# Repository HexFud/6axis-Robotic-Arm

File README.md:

## 6 Axis Robotic Arm

I created this 6 axis robotic arm entirely from scratch starting from the PCB to the 3D modelling and designing.

## How this was made

I designed the PCB that can take up to 6 motors (I used 6 NEMA 17) with 6 driver boards that you can directly plug into the PCB. In the PCB case there is a cutout for a 40mm fan directly pluggable into the dedicated +5V socket (identified by FAN or J8 connector), this is foundamental to keep the motor drivers cool and keep things as safe as possible. The board runs on 24V connection and includes connections for:

1. **6 limit switches** for homing each joint
2. **A CAN Bus interface**
3. **An emergency stop button socket** for safety reason. 

## External connections breakdown

1. **E-STOP (J21)** The emergency stop circuit is NC so the board without this button won't power on, if you want to avoid this you can short 2 pins of the J21 connector with a jumper (please mind your safety)
2. **CAN Bus (J22)** This is the port to make the PCB comunicate with the PC and it only has 2 pins CAN_H and CAN_L if you want to send commands directly to the board you need to have a USB-CAN adapter
3. **Power button (J19)** The socket on the PCB has 4 pins
 
| Pin | Function | Where to connect |
| :---: | :--- | :--- |
| **1** | `GND` | Switch contact + LED Negative (`-`) wire |
| **2** | `PWR` | Switch contact |
| **3** | `+3V3` | LED Positive (`+`) wire |
| **4** | `Reserved` | *Do not connect any wire to it* |

## Mechanical design and why I chose certain components

To make sure the arm can lift certain payloads wihout struggling I preferred to not use a direct-drive style to move the joints, this is why for the most heavy and tourqe demanding parts I paired the NEMA 17 motors with 20:1 and 10:1 gearboxes (you can see them marked in red)

## How to flash the firmware

My project doesn't have a USB-C or other type of interfaces so to flash the firmware you need a ST-LINK V2 where you need to wire up the correct cable from the usb to the board (J18 connector) and download the free software [STM32CubeProgrammer](https://www.st.com/content/st_com/en/stm32cubeprogrammer.html) and you simply need to upload the firmware.

Steps to reproduce (note that you need to do both):

In Arduino IDE:
1. Install Arduino IDE
2. Paste https://github.com/stm32duino/BoardManagerFiles/raw/main/package_stmicroelectronics_index.json into prefernces -> additional board manager URL's
3. Search STM32 into the boards stab and install it
4. Go in tools -> board -> STM32 MCU based boards and select Generic STM32F4 series
5. Go in tools -> board part number and select Generic F446RETx
6. Go to sketch -> export compiled binary

In STM32CubeProgrammer:
1. Install the software from the link above
2. Insert the ST-Link V2 USB into the pc
3. Connect the pins explained above (do not connect the 24V power supply, the ST-Link has enough power to power the chip to flash)
4. In STM32CubeProgrammer ensure that ST-LINK is selected and click connect
5. Go in the erasing & programming tab and select the previously exported .bin file
6. Click start programming and if everything went right you'll see Download verified successfully

## Filament reccomendation

Because stepper motors and the drivers generate heat around 50°C-60°C I strongly reccomend to use filaments like PETG, ABS or ASA instead of standard PLA ensuring the plastic won't soften, warp or melt during intensive load.

## ⚠️⚠️ Safety advice ⚠️⚠️

This project includes experimental software, hardware designs, and assembly documentation are still under development and may contain bugs, errors, or incomplete features. By using, building, or modifying this project, you acknowledge that:

1. You use this project entirely at your own risk
2. You are solely responsible for safe assembly, testing, and operation
3. The autor isn't responsible for any type of damage, injury or loss to people or the machine itself

By proceeding, you accept all risks and agree to these conditions. If you do not acknowledge these risks and conditions, please do not use or build this project.

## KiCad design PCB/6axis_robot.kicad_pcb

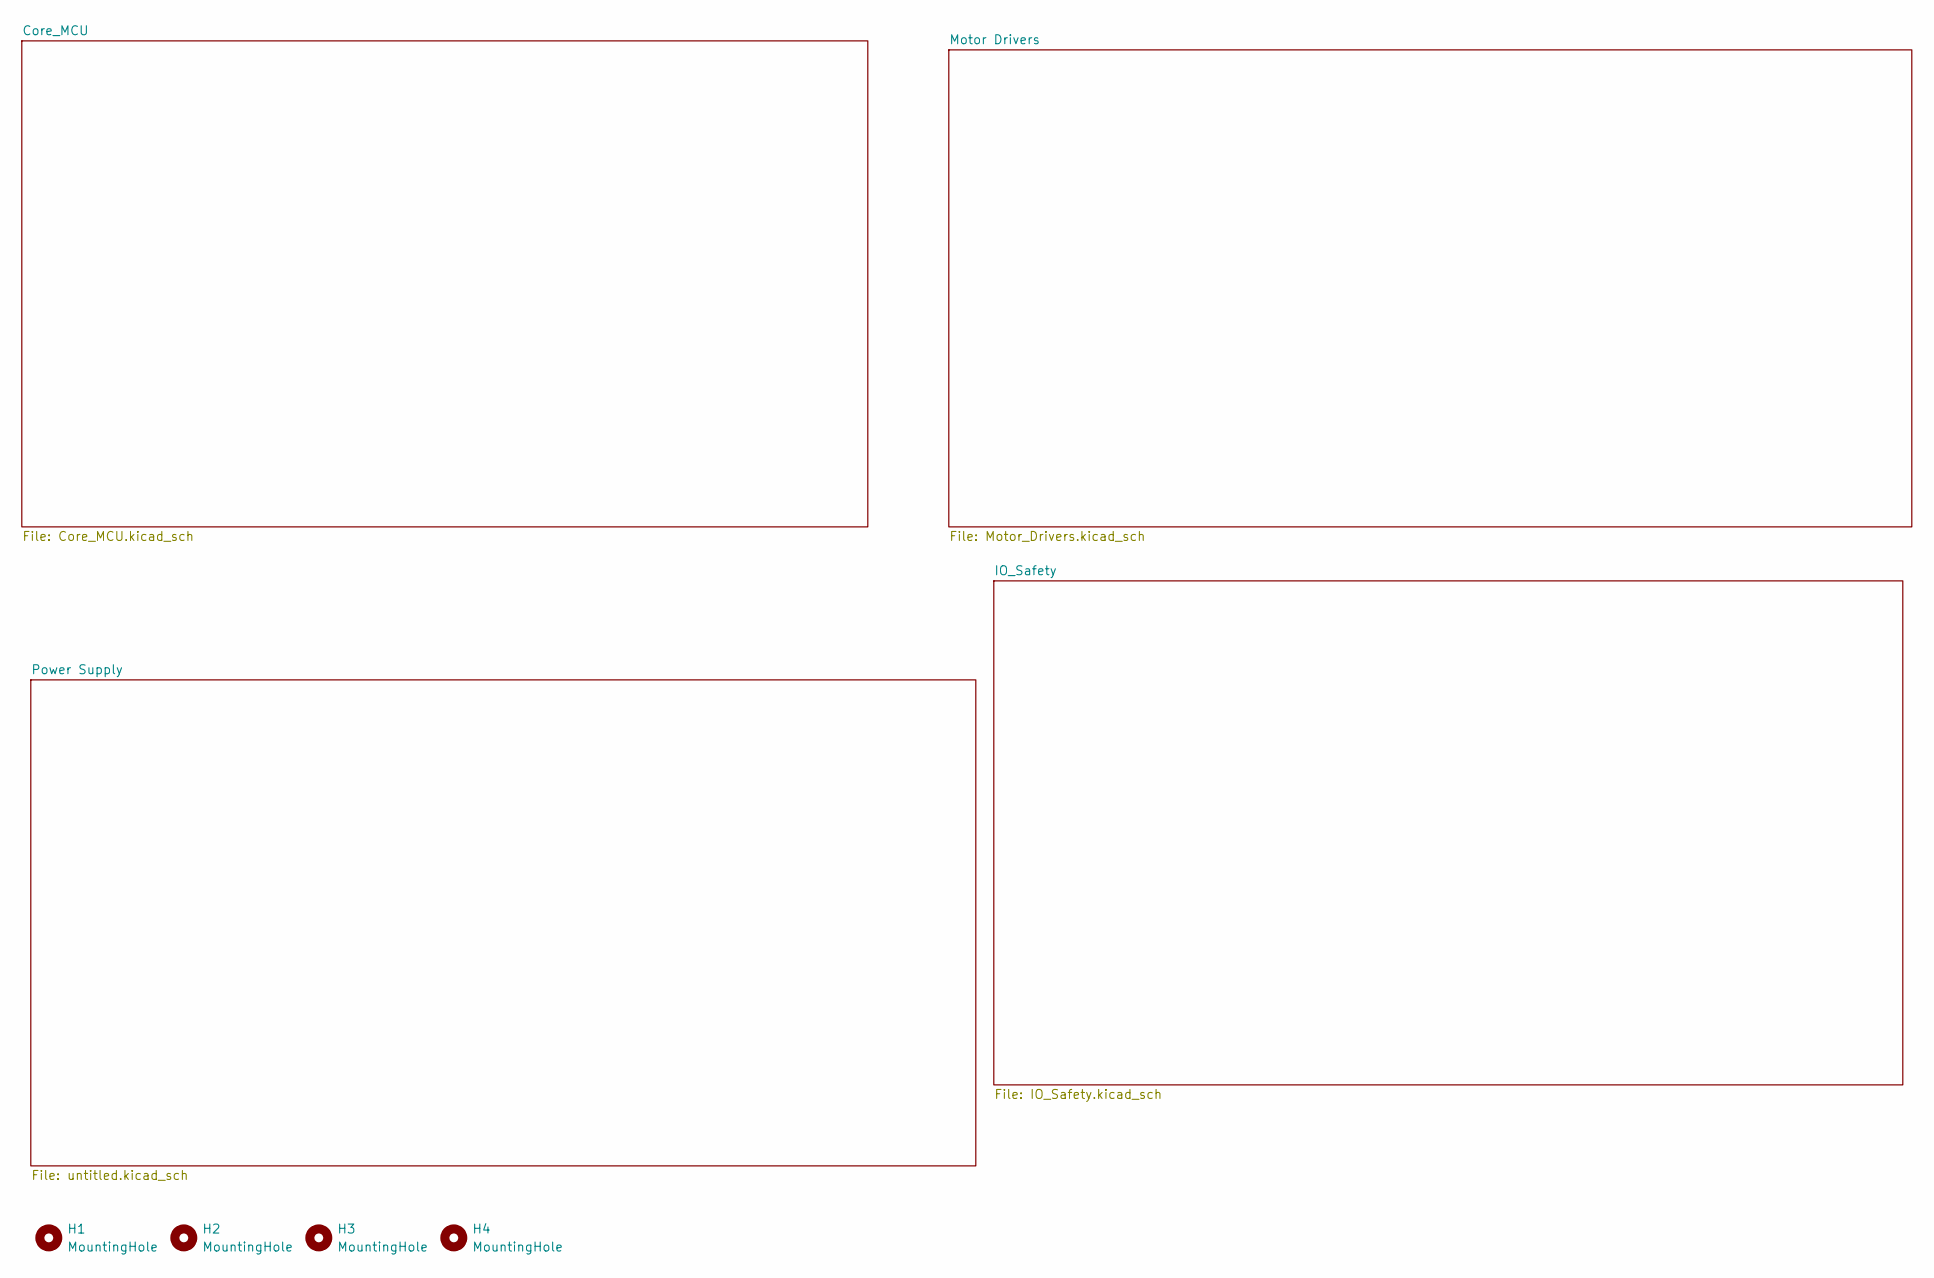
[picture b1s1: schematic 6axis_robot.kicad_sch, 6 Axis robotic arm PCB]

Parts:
H1, H2, H3, H4: MountingHole; MountingHole_3.2mm_M3

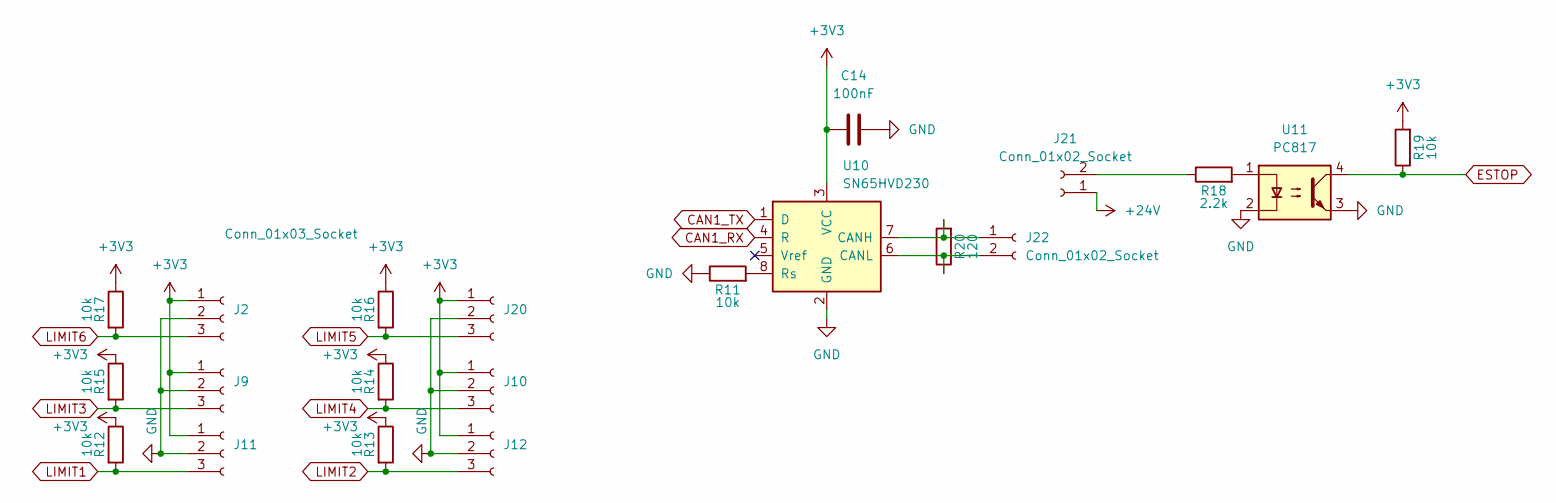
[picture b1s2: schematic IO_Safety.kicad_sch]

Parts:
C14: 100nF; C_0805_2012Metric
J2, J9, J10, J11, J12, J20: Conn_01x03_Socket; JST_XH_B3B-XH-A_1x03_P2.50mm_Vertical
J21, J22: Conn_01x02_Socket; JST_XH_B2B-XH-A_1x02_P2.50mm_Vertical
R11, R12, R13, R14, R15, R16, R17, R19: 10k; R_0805_2012Metric
R18: 2.2k; R_0805_2012Metric
R20: 120; R_0805_2012Metric
U10: SN65HVD230; SOIC-8_3.9x4.9mm_P1.27mm
U11: PC817; DIP-4_W7.62mm

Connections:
+3V3: C14.1, J2.1, J9.1, J10.1, J11.1, J12.1, J20.1, R12.1, R13.1, R14.1, R15.1, R16.1, R17.1, R19.2, U10.3 (VCC); also elsewhere on the board
+24V: J21.1; also elsewhere on the board
CAN1_RX: U10.4 (R); also elsewhere on the board
CAN1_TX: U10.1 (D); also elsewhere on the board
ESTOP: R19.1, U11.4; also elsewhere on the board
GND: C14.2, J2.2, J9.2, J10.2, J11.2, J12.2, J20.2, R11.1, U10.2 (GND), U11.2, U11.3; also elsewhere on the board
LIMIT1: J11.3, R12.2; also elsewhere on the board
LIMIT2: J12.3, R13.2; also elsewhere on the board
LIMIT3: J9.3, R15.2; also elsewhere on the board
LIMIT4: J10.3, R14.2; also elsewhere on the board
LIMIT5: J20.3, R16.2; also elsewhere on the board
LIMIT6: J2.3, R17.2; also elsewhere on the board
unnamed: J21.2, R18.1
unnamed: J22.1, R20.2, U10.7 (CANH)
unnamed: J22.2, R20.1, U10.6 (CANL)
unnamed: R18.2, U11.1
unnamed: R11.2, U10.8 (Rs)

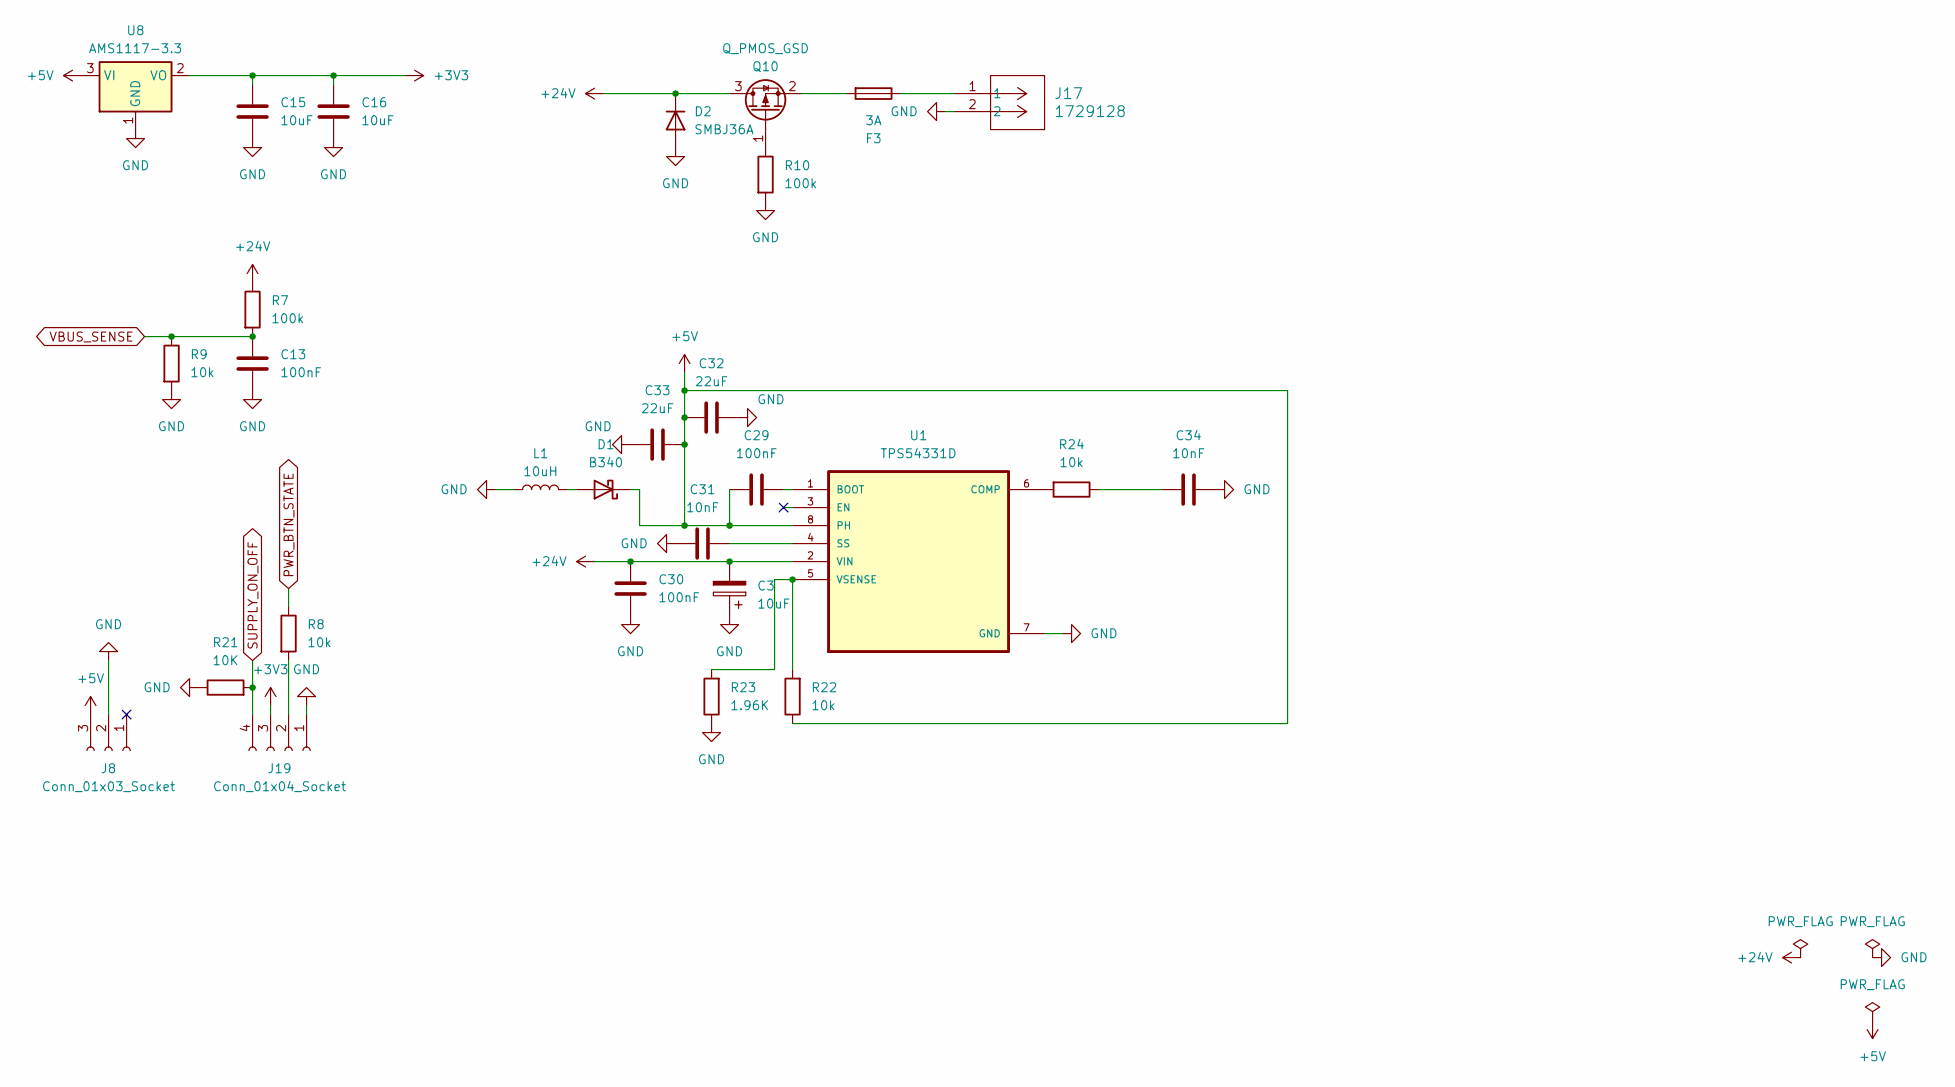
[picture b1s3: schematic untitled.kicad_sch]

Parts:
C3: 10uF; CP_Radial_D6.3mm_P2.50mm
C13, C29, C30: 100nF; C_0805_2012Metric
C15, C16: 10uF; C_0805_2012Metric
C31, C34: 10nF; C_0805_2012Metric
C32, C33: 22uF; C_0805_2012Metric
D1: B340; D_SMC
D2: SMBJ36A; D_SMB
F3: 3A; Fuse_1812_4532Metric
J8: Conn_01x03_Socket; JST_XH_B3B-XH-A_1x03_P2.50mm_Vertical
J17: 1729128; CONN_1729128_PXC
J19: Conn_01x04_Socket; JST_PH_B4B-PH-K_1x04_P2.00mm_Vertical
L1: 10uH; L_Sunlord_SWPA6045S
Q10: Q_PMOS_GSD; SOT-23
R7, R10: 100k; R_0805_2012Metric
R8, R9, R22, R24: 10k; R_0805_2012Metric
R21: 10K; R_0805_2012Metric
R23: 1.96K; R_0805_2012Metric
U1: TPS54331D; SOIC127P599X175-8N
U8: AMS1117-3.3; SOT-223-3_TabPin2

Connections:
+3V3: C15.2, C16.2, J19.3, U8.2 (VO); also elsewhere on the board
+5V: C29.1, C32.1, C33.2, D1.1 (K), J8.3, R22.1, U1.8 (PH), U8.3 (VI)
+24V: C3.2, C30.1, D2.1 (K), Q10.3 (D), R7.1, U1.2 (VIN); also elsewhere on the board
GND: C3.1, C13.2, C15.1, C16.1, C30.2, C31.1, C32.2, C33.1, C34.2, D2.2 (A), J8.2, J17.2, J19.1, L1.1, R9.2, R10.2, R21.1, R23.1, U1.7 (GND), U8.1 (GND); also elsewhere on the board
unnamed: C34.1, R24.1
unnamed: D1.2 (A), L1.2
unnamed: F3.1, J17.1
unnamed: J19.2, R8.2
unnamed: Q10.1 (G), R10.1
unnamed: F3.2, Q10.2 (S)
unnamed: C29.2, U1.1 (BOOT)
unnamed: R24.2, U1.6 (COMP)
unnamed: C31.2, U1.4 (SS)
unnamed: R22.2, R23.2, U1.5 (VSENSE)
PWR_BTN_STATE: R8.1; also elsewhere on the board
SUPPLY_ON_OFF: J19.4, R21.2; also elsewhere on the board
VBUS_SENSE: C13.1, R7.2, R9.1; also elsewhere on the board

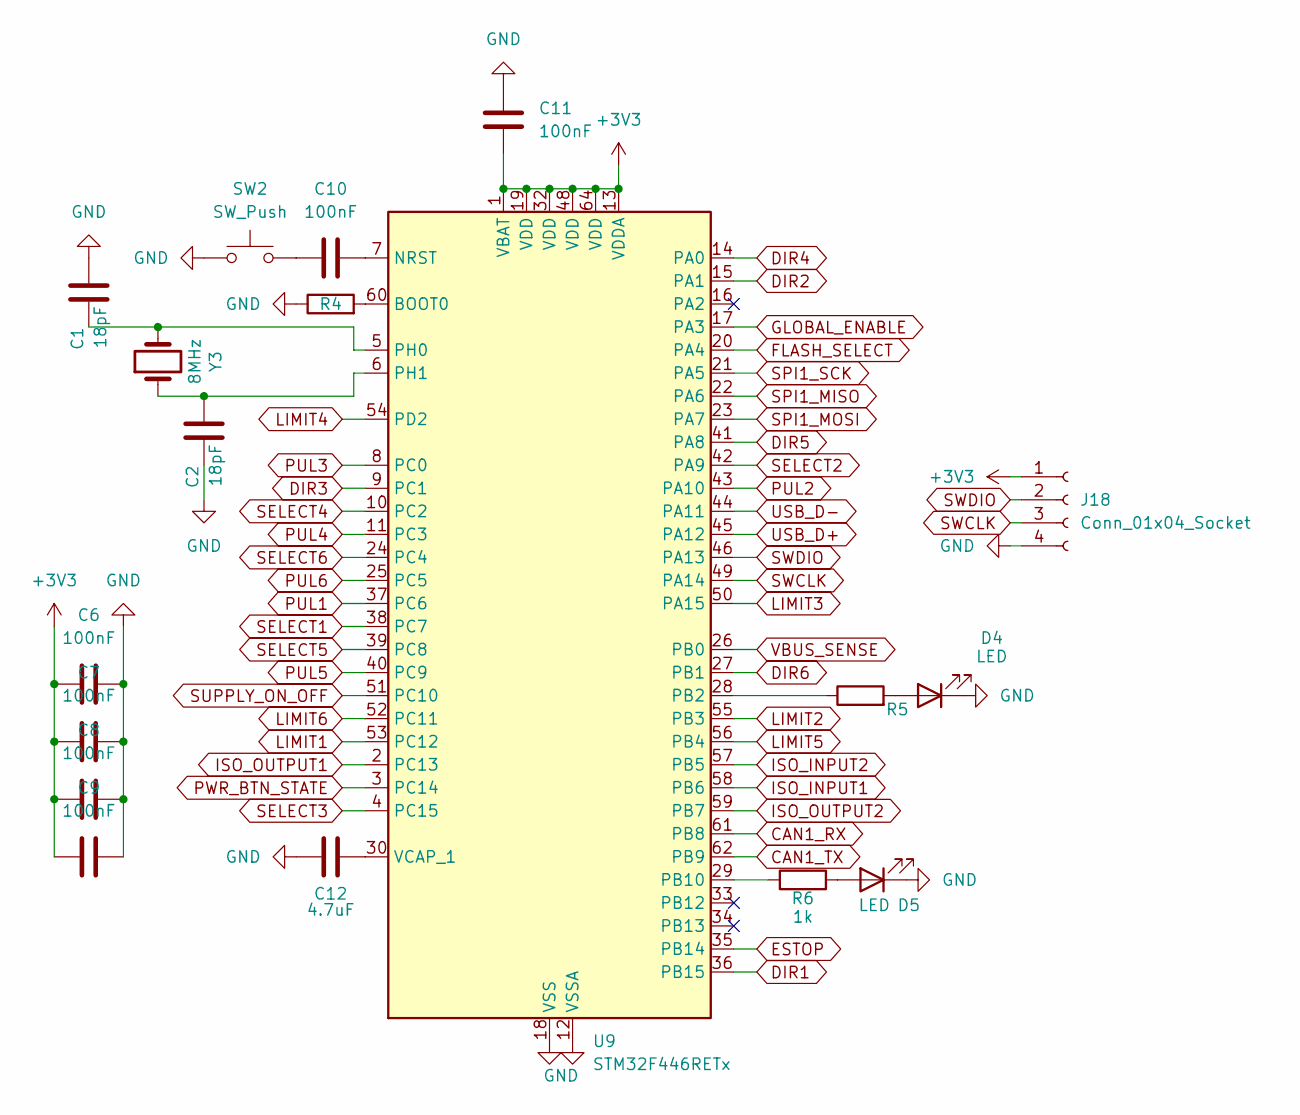
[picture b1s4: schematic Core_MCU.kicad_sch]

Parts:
C1, C2: 18pF; C_0805_2012Metric
C6, C7, C8, C9, C10, C11: 100nF; C_0805_2012Metric
C12: 4.7uF; C_0805_2012Metric
D4, D5: LED; LED_0805_2012Metric
J18: Conn_01x04_Socket; PinHeader_1x04_P2.54mm_Vertical
R4: 10k; R_0805_2012Metric
R5, R6: 1k; R_0805_2012Metric
SW2: SW_Push; SW_PUSH_6mm
U9: STM32F446RETx; LQFP-64_10x10mm_P0.5mm
Y3: 8MHz; Crystal_SMD_5032-2Pin_5.0x3.2mm

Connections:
+3V3: C6.2, C7.2, C8.2, C9.2, C11.2, J18.1, U9.1 (VBAT), U9.13 (VDDA), U9.19 (VDD), U9.32 (VDD), U9.48 (VDD), U9.64 (VDD); also elsewhere on the board
CAN1_RX: U9.61 (PB8); also elsewhere on the board
CAN1_TX: U9.62 (PB9); also elsewhere on the board
DIR1: U9.36 (PB15); also elsewhere on the board
DIR2: U9.15 (PA1); also elsewhere on the board
DIR3: U9.9 (PC1); also elsewhere on the board
DIR4: U9.14 (PA0); also elsewhere on the board
DIR5: U9.41 (PA8); also elsewhere on the board
DIR6: U9.27 (PB1); also elsewhere on the board
ESTOP: U9.35 (PB14); also elsewhere on the board
FLASH_SELECT: U9.20 (PA4)
GLOBAL_ENABLE: U9.17 (PA3); also elsewhere on the board
GND: C1.2, C2.1, C6.1, C7.1, C8.1, C9.1, C11.1, C12.1, D4.1 (K), D5.1 (K), J18.4, R4.1, SW2.1, U9.12 (VSSA), U9.18 (VSS), U9.31 (VSS), U9.47 (VSS), U9.63 (VSS); also elsewhere on the board
ISO_INPUT1: U9.58 (PB6)
ISO_INPUT2: U9.57 (PB5)
ISO_OUTPUT1: U9.2 (PC13)
ISO_OUTPUT2: U9.59 (PB7)
LIMIT1: U9.53 (PC12); also elsewhere on the board
LIMIT2: U9.55 (PB3); also elsewhere on the board
LIMIT3: U9.50 (PA15); also elsewhere on the board
LIMIT4: U9.54 (PD2); also elsewhere on the board
LIMIT5: U9.56 (PB4); also elsewhere on the board
LIMIT6: U9.52 (PC11); also elsewhere on the board
unnamed: C10.2, SW2.2
unnamed: D4.2 (A), R5.2
unnamed: D5.2 (A), R6.2
unnamed: R4.2, U9.60 (BOOT0)
unnamed: C10.1, U9.7 (NRST)
unnamed: R5.1, U9.28 (PB2)
unnamed: R6.1, U9.29 (PB10)
unnamed: C1.1, U9.5 (PH0), Y3.2
unnamed: C2.2, U9.6 (PH1), Y3.1
unnamed: C12.2, U9.30 (VCAP_1)
PUL1: U9.37 (PC6); also elsewhere on the board
PUL2: U9.43 (PA10); also elsewhere on the board
PUL3: U9.8 (PC0); also elsewhere on the board
PUL4: U9.11 (PC3); also elsewhere on the board
PUL5: U9.40 (PC9); also elsewhere on the board
PUL6: U9.25 (PC5); also elsewhere on the board
PWR_BTN_STATE: U9.3 (PC14); also elsewhere on the board
SELECT1: U9.38 (PC7); also elsewhere on the board
SELECT2: U9.42 (PA9); also elsewhere on the board
SELECT3: U9.4 (PC15); also elsewhere on the board
SELECT4: U9.10 (PC2); also elsewhere on the board
SELECT5: U9.39 (PC8); also elsewhere on the board
SELECT6: U9.24 (PC4); also elsewhere on the board
SPI1_MISO: U9.22 (PA6); also elsewhere on the board
SPI1_MOSI: U9.23 (PA7); also elsewhere on the board
SPI1_SCK: U9.21 (PA5); also elsewhere on the board
SUPPLY_ON_OFF: U9.51 (PC10); also elsewhere on the board
SWCLK: J18.3, U9.49 (PA14)
SWDIO: J18.2, U9.46 (PA13)
USB_D+: U9.45 (PA12)
USB_D-: U9.44 (PA11)
VBUS_SENSE: U9.26 (PB0); also elsewhere on the board

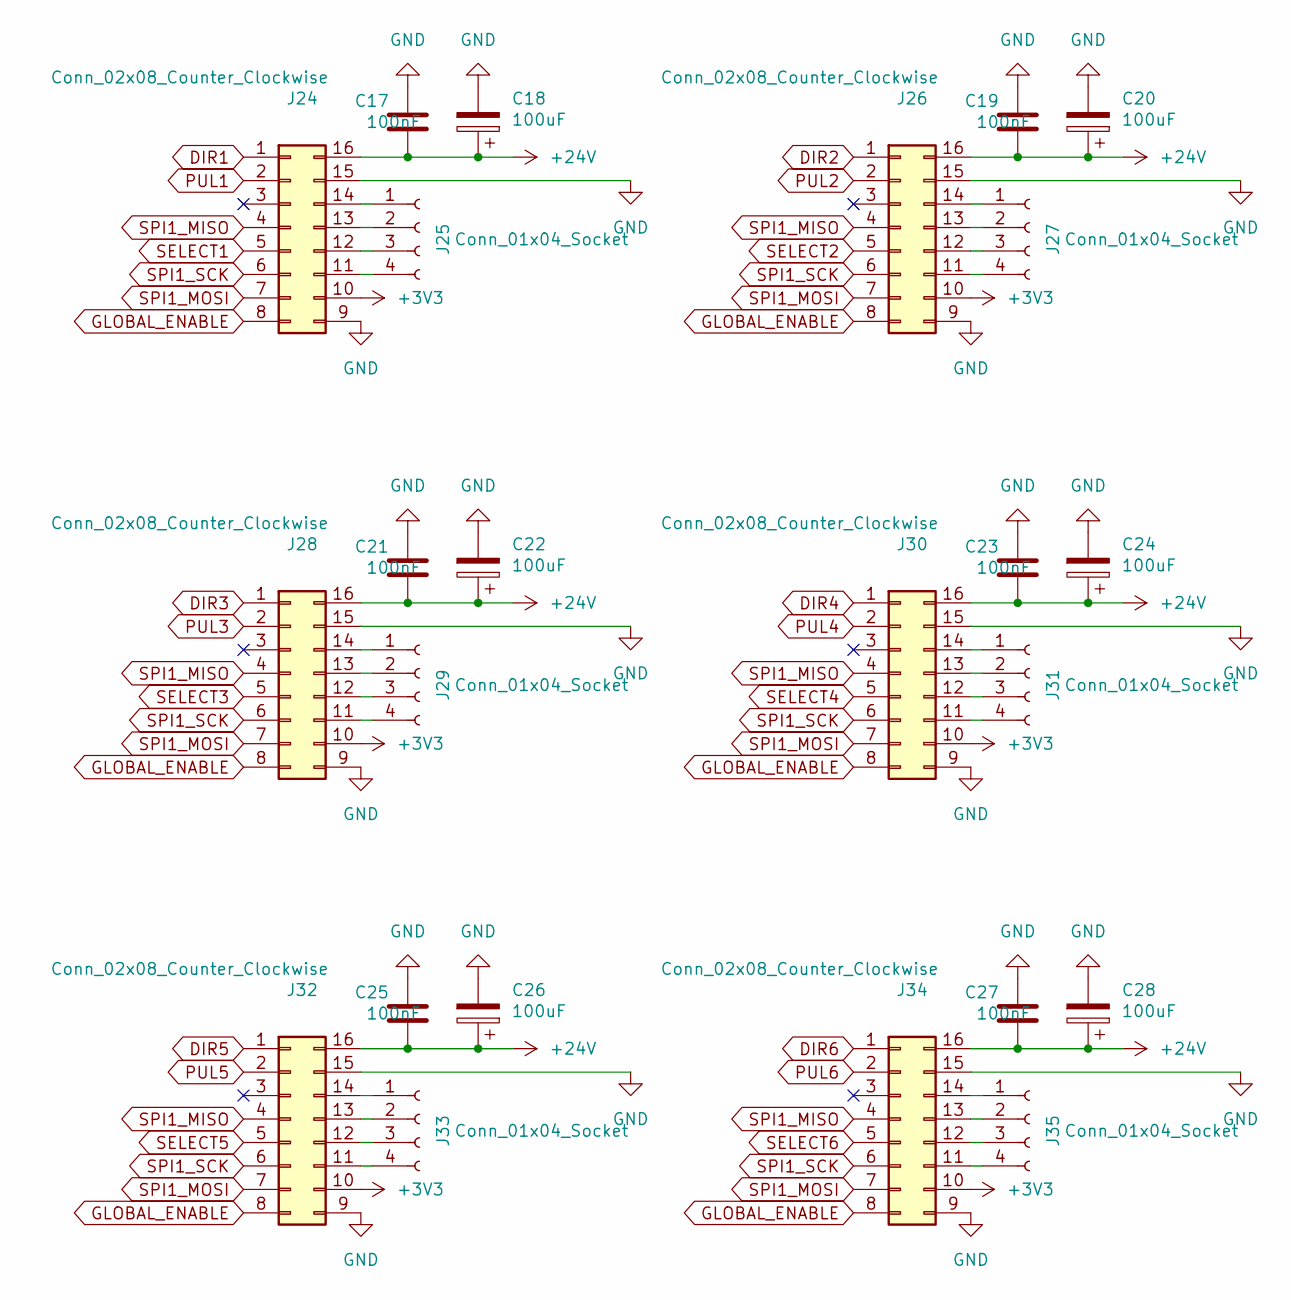
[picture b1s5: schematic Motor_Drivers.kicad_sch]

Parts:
C17, C19, C21, C23, C25, C27: 100nF; C_0805_2012Metric
C18, C20, C22, C24, C26, C28: 100uF; CP_Radial_D6.3mm_P2.50mm
J24, J26, J28, J30, J32, J34: Conn_02x08_Counter_Clockwise; 8825
J25, J27, J29, J31, J33, J35: Conn_01x04_Socket; JST_XH_B4B-XH-A_1x04_P2.50mm_Vertical

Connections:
+3V3: J24.10, J26.10, J28.10, J30.10, J32.10, J34.10; also elsewhere on the board
+24V: C17.2, C18.1, C19.2, C20.1, C21.2, C22.1, C23.2, C24.1, C25.2, C26.1, C27.2, C28.1, J24.16, J26.16, J28.16, J30.16, J32.16, J34.16; also elsewhere on the board
DIR1: J24.1; also elsewhere on the board
DIR2: J26.1; also elsewhere on the board
DIR3: J28.1; also elsewhere on the board
DIR4: J30.1; also elsewhere on the board
DIR5: J32.1; also elsewhere on the board
DIR6: J34.1; also elsewhere on the board
GLOBAL_ENABLE: J24.8, J26.8, J28.8, J30.8, J32.8, J34.8; also elsewhere on the board
GND: C17.1, C18.2, C19.1, C20.2, C21.1, C22.2, C23.1, C24.2, C25.1, C26.2, C27.1, C28.2, J24.9, J24.15, J26.9, J26.15, J28.9, J28.15, J30.9, J30.15, J32.9, J32.15, J34.9, J34.15; also elsewhere on the board
unnamed: J24.11, J25.4
unnamed: J24.12, J25.3
unnamed: J24.13, J25.2
unnamed: J24.14, J25.1
unnamed: J26.11, J27.4
unnamed: J26.12, J27.3
unnamed: J26.13, J27.2
unnamed: J26.14, J27.1
unnamed: J28.11, J29.4
unnamed: J28.12, J29.3
unnamed: J28.13, J29.2
unnamed: J28.14, J29.1
unnamed: J30.11, J31.4
unnamed: J30.12, J31.3
unnamed: J30.13, J31.2
unnamed: J30.14, J31.1
unnamed: J32.11, J33.4
unnamed: J32.12, J33.3
unnamed: J32.13, J33.2
unnamed: J32.14, J33.1
unnamed: J34.11, J35.4
unnamed: J34.12, J35.3
unnamed: J34.13, J35.2
unnamed: J34.14, J35.1
PUL1: J24.2; also elsewhere on the board
PUL2: J26.2; also elsewhere on the board
PUL3: J28.2; also elsewhere on the board
PUL4: J30.2; also elsewhere on the board
PUL5: J32.2; also elsewhere on the board
PUL6: J34.2; also elsewhere on the board
SELECT1: J24.5; also elsewhere on the board
SELECT2: J26.5; also elsewhere on the board
SELECT3: J28.5; also elsewhere on the board
SELECT4: J30.5; also elsewhere on the board
SELECT5: J32.5; also elsewhere on the board
SELECT6: J34.5; also elsewhere on the board
SPI1_MISO: J24.4, J26.4, J28.4, J30.4, J32.4, J34.4; also elsewhere on the board
SPI1_MOSI: J24.7, J26.7, J28.7, J30.7, J32.7, J34.7; also elsewhere on the board
SPI1_SCK: J24.6, J26.6, J28.6, J30.6, J32.6, J34.6; also elsewhere on the board

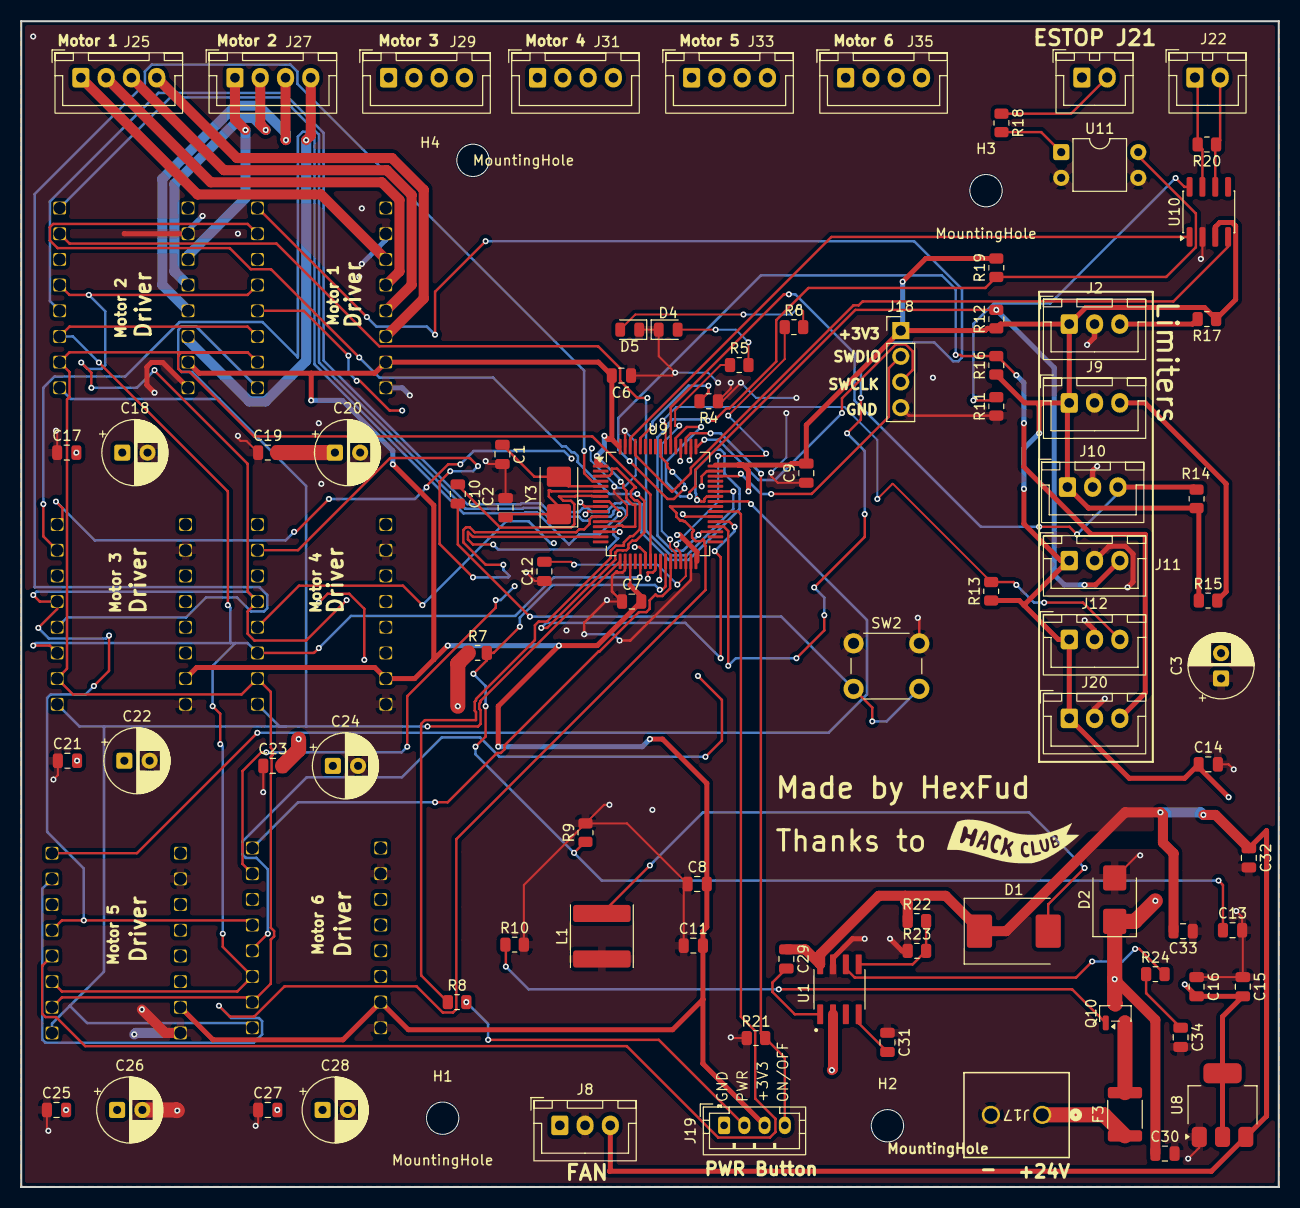
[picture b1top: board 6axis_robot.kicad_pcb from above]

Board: 4 copper layers, 124.4 x 115.3 mm, 95 parts (0 on the bottom side), 89 nets.

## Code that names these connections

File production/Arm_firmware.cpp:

#include <Arduino.h>

#define GLOBAL_ENABLE_PIN  PA3
#define STEP1_PIN          PC6
#define DIR1_PIN           PB15
#define CS1_PIN            PC7
#define STEP2_PIN          PC5
#define DIR2_PIN           PB1
#define CS2_PIN            PC4
#define STEP3_PIN          PC9
#define DIR3_PIN           PA8
#define CS3_PIN            PC8
#define STEP4_PIN          PC3
#define DIR4_PIN           PA0
#define CS4_PIN            PC2
#define STEP5_PIN          PA10
#define DIR5_PIN           PA1
#define CS5_PIN            PA9
#define STEP6_PIN          PC0
#define DIR6_PIN           PC1
#define CS6_PIN            PC15

#define LED_BLUE           PB2
#define LED_RED            PB10
#define ESTOP_PIN          PB14
#define SUPPLY_ON_OFF      PC10

void setup() {
  pinMode(LED_BLUE, OUTPUT);
  pinMode(LED_RED, OUTPUT);
  
  pinMode(SUPPLY_ON_OFF, OUTPUT);
  digitalWrite(SUPPLY_ON_OFF, HIGH); 

  pinMode(ESTOP_PIN, INPUT_PULLUP);

  pinMode(GLOBAL_ENABLE_PIN, OUTPUT);
  
  pinMode(STEP1_PIN, OUTPUT); pinMode(DIR1_PIN, OUTPUT); pinMode(CS1_PIN, OUTPUT);
  pinMode(STEP2_PIN, OUTPUT); pinMode(DIR2_PIN, OUTPUT); pinMode(CS2_PIN, OUTPUT);
  pinMode(STEP3_PIN, OUTPUT); pinMode(DIR3_PIN, OUTPUT); pinMode(CS3_PIN, OUTPUT);
  pinMode(STEP4_PIN, OUTPUT); pinMode(DIR4_PIN, OUTPUT); pinMode(CS4_PIN, OUTPUT);
  pinMode(STEP5_PIN, OUTPUT); pinMode(DIR5_PIN, OUTPUT); pinMode(CS5_PIN, OUTPUT);
  pinMode(STEP6_PIN, OUTPUT); pinMode(DIR6_PIN, OUTPUT); pinMode(CS6_PIN, OUTPUT);

  digitalWrite(CS1_PIN, HIGH); digitalWrite(CS2_PIN, HIGH);
  digitalWrite(CS3_PIN, HIGH); digitalWrite(CS4_PIN, HIGH);
  digitalWrite(CS5_PIN, HIGH); digitalWrite(CS6_PIN, HIGH);

  digitalWrite(GLOBAL_ENABLE_PIN, LOW);
}

void loop() {
  if (digitalRead(ESTOP_PIN) == LOW) {
    digitalWrite(GLOBAL_ENABLE_PIN, HIGH);
    digitalWrite(LED_RED, HIGH);
    digitalWrite(LED_BLUE, LOW);
    delay(500);
    return; 
  }

  digitalWrite(LED_RED, LOW);
  
  digitalWrite(DIR1_PIN, HIGH); digitalWrite(DIR2_PIN, HIGH); digitalWrite(DIR3_PIN, HIGH);
  digitalWrite(DIR4_PIN, HIGH); digitalWrite(DIR5_PIN, HIGH); digitalWrite(DIR6_PIN, HIGH);

  for (int i = 0; i < 3200; i++) {
    digitalWrite(STEP1_PIN, HIGH); digitalWrite(STEP2_PIN, HIGH); digitalWrite(STEP3_PIN, HIGH);
    digitalWrite(STEP4_PIN, HIGH); digitalWrite(STEP5_PIN, HIGH); digitalWrite(STEP6_PIN, HIGH);
    delayMicroseconds(500); 
    
    digitalWrite(STEP1_PIN, LOW); digitalWrite(STEP2_PIN, LOW); digitalWrite(STEP3_PIN, LOW);
    digitalWrite(STEP4_PIN, LOW); digitalWrite(STEP5_PIN, LOW); digitalWrite(STEP6_PIN, LOW);
    delayMicroseconds(500);
  }

  digitalWrite(LED_BLUE, HIGH);
  delay(500);
  digitalWrite(LED_BLUE, LOW);

  digitalWrite(DIR1_PIN, LOW); digitalWrite(DIR2_PIN, LOW); digitalWrite(DIR3_PIN, LOW);
  digitalWrite(DIR4_PIN, LOW); digitalWrite(DIR5_PIN, LOW); digitalWrite(DIR6_PIN, LOW);

  for (int i = 0; i < 3200; i++) {
    digitalWrite(STEP1_PIN, HIGH); digitalWrite(STEP2_PIN, HIGH); digitalWrite(STEP3_PIN, HIGH);
    digitalWrite(STEP4_PIN, HIGH); digitalWrite(STEP5_PIN, HIGH); digitalWrite(STEP6_PIN, HIGH);
    delayMicroseconds(500);
    digitalWrite(STEP1_PIN, LOW); digitalWrite(STEP2_PIN, LOW); digitalWrite(STEP3_PIN, LOW);
    digitalWrite(STEP4_PIN, LOW); digitalWrite(STEP5_PIN, LOW); digitalWrite(STEP6_PIN, LOW);
    delayMicroseconds(500);
  }

  delay(1000); 
}
